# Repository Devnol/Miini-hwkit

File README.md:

# Miini hwkit
 Hardware schematics and PCB drawings for Nintendo Wii mini console add-ons.
 
### Project has moved permanently
 You can view the latest version [here](https://github.com/Wii-Mini-Hacking/miniRGBii)

 For more information visit [the Wii mini Hacking discord server](https://discord.gg/7jNHphfDQk)

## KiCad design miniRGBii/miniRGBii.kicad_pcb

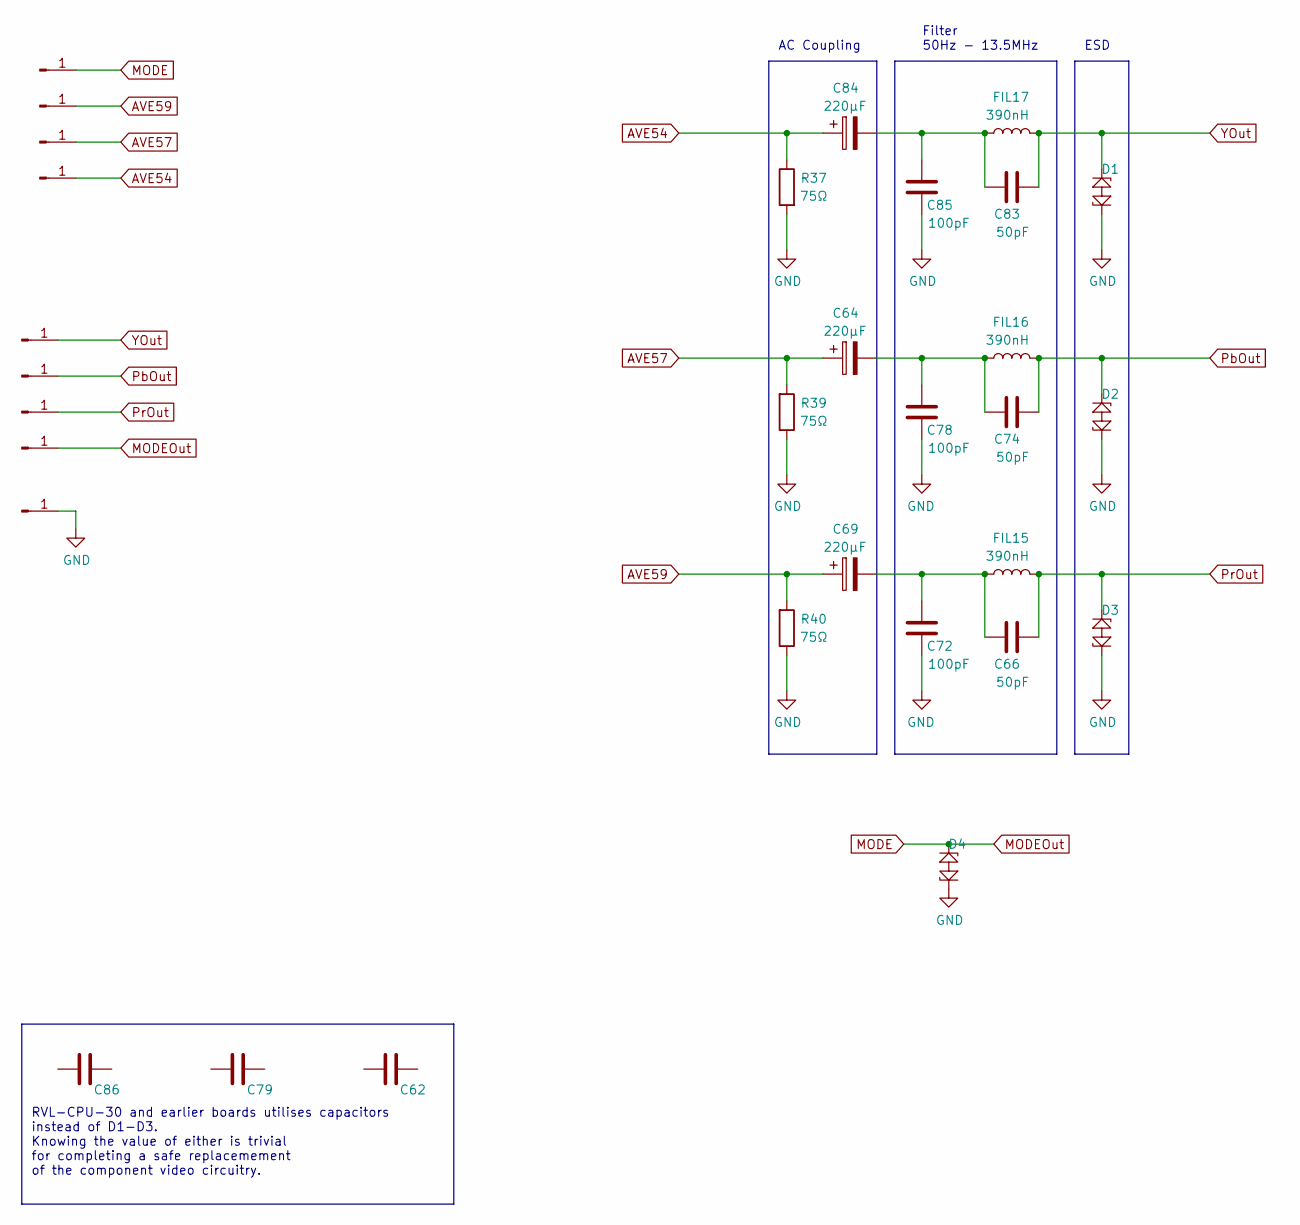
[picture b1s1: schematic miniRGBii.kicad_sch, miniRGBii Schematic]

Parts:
C62, C79, C86: 50pF
C64, C69, C84: 220μF; CP_EIA-7343-15_Kemet-W_Pad2.25x2.55mm_HandSolder
C66, C74, C83: 50pF; C_0603_1608Metric_Pad1.05x0.95mm_HandSolder
C72, C78, C85: 100pF; C_0603_1608Metric_Pad1.05x0.95mm_HandSolder
D1, D2, D3, D4: PESD5V0U1BA; D_SOD-323_HandSoldering
FIL15, FIL16, FIL17: 390nH; L_0603_1608Metric_Pad1.05x0.95mm_HandSolder
J1, J2, J3, J4, J5, J6, J7, J8, J9: Conn_01x01_Male; pad
R37, R39, R40: 75Ω; R_0603_1608Metric_Pad0.98x0.95mm_HandSolder

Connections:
AVE54: C84.1, J8.1, R37.1
AVE57: C64.1, J7.1, R39.2
AVE59: C69.1, J6.1, R40.2
GND: C72.1, C78.1, C85.1, D1.2, D2.2, D3.2, D4.2, J9.1, R37.2, R39.1, R40.1
MODE: D4.1, J4.1, J5.1
unnamed: C64.2, C74.1, C78.2, FIL16.2
unnamed: C66.1, C69.2, C72.2, FIL15.2
unnamed: C83.1, C84.2, C85.2, FIL17.2
PbOut: C74.2, D2.1, FIL16.1, J2.1
PrOut: C66.2, D3.1, FIL15.1, J3.1
YOut: C83.2, D1.1, FIL17.1, J1.1

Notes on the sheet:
RVL-CPU-30 and earlier boards utilises capacitors instead of D1-D3. Knowing the value of either is trivial for completing a safe replacemement of the component video circuitry.
Filter 50Hz - 13.5MHz
ESD
AC Coupling

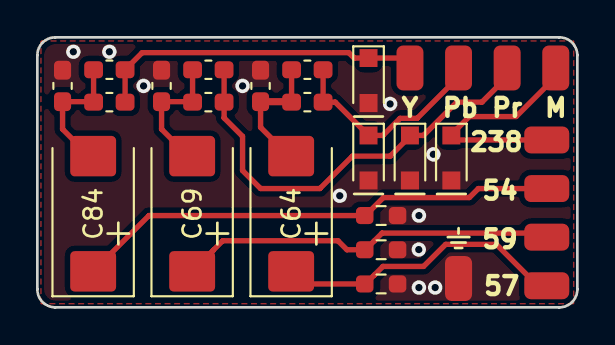
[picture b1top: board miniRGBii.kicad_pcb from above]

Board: 2 copper layers, 30.0 x 15.0 mm, 28 parts (0 on the bottom side), 11 nets.

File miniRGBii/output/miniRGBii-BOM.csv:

"Source:","/Users/User/Documents/CS_Projects/EDA/Miini-hwkit/miniRGBii/miniRGBii.kicad_sch"
"Date:","2022 February 26, Saturday 19:09:56"
"Tool:","Eeschema (6.0.0-0)"
"Generator:","/Applications/KiCad/KiCad.app/Contents/SharedSupport/plugins/bom_csv_grouped_by_value_with_fp.py"
"Component Count:","31"
"Ref","Qnty","Value","Cmp name","Footprint","Description","Vendor"
"C62, C79, C86, ","3","50pF","C","","Unpolarized capacitor",""
"C64, C69, C84, ","3","220μF","C_Polarized","Capacitor_Tantalum_SMD:CP_EIA-7343-15_Kemet-W_Pad2.25x2.55mm_HandSolder","Polarized capacitor",""
"C66, C74, C83, ","3","50pF","C","Capacitor_SMD:C_0603_1608Metric_Pad1.05x0.95mm_HandSolder","Unpolarized capacitor",""
"C72, C78, C85, ","3","100pF","C","Capacitor_SMD:C_0603_1608Metric_Pad1.05x0.95mm_HandSolder","Unpolarized capacitor",""
"D1, D2, D3, D4, ","4","PESD5V0U1BA","PESD5V0U1BA","Diode_SMD:D_SOD-323_HandSoldering","",""
"FIL15, FIL16, FIL17, ","3","390nH","L","Inductor_SMD:L_0603_1608Metric_Pad1.05x0.95mm_HandSolder","Inductor",""
"J1, J2, J3, J4, J5, J6, J7, J8, J9, ","9","Conn_01x01_Male","Conn_01x01_Male","Pad:pad","Generic connector, single row, 01x01, script generated (kicad-library-utils/schlib/autogen/connector/)",""
"R37, R39, R40, ","3","75Ω","R","Resistor_SMD:R_0603_1608Metric_Pad0.98x0.95mm_HandSolder","Resistor",""

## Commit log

2020-05-26 Added HDTVii, an add-on board for Component video (Incomplete, untested)
2020-05-26 Updated SVG and PDF files
2020-06-04 forgotten to commit this idk
2020-06-30 Changed some stuff around I guess
2020-06-30 Added footprints
2020-07-06 Added correct (hopefully) inductor values. Credit to Job Feikens for the values
2020-07-09 Created PCB design and added footprint refs to parts.
    Also changed stuff in the Schematic
2020-07-09 Renamed project, trimmed pcb design
2020-07-23 Changed many things
2020-07-23 Added PDF and SVG for easy viewing
2020-07-28 Changed schematic to look less tangled
2020-07-28 At least there's the net on pcbnew to remind me how big of a moron I am.
    I had mixed up some parts while shifting the schematic around/
2020-07-28 Changed the board to utilise lower profile capacitors
2020-08-28 Removed everything from the master branch
2020-08-28 Copied Job's design to the master branch and changed the naming of the designs
2020-08-29 removed old rear solder mask gerbers
2020-08-29 Added 20-pack stencil for large production.
    Also moved a GND via that was too close to a data line
2020-08-30 renamed to panel cuz I'm dumb
2020-08-30 added images folder for people without KiCAD and made curved edges
2020-08-30 Changed url to lowercase, moved vias around
2020-08-30 finalised (hopefully) the panel version
2020-08-30 made a new output.zip
2020-12-07 added gitignore
2020-12-07 edited gitignore
2020-12-09 mentioned wiiniidsdii
2020-12-09 Added files
2020-12-14 Rename WiiNiidSDii/.gitkeep to WiiniSDii
2020-12-14 Create ,gitkeep
2021-01-07 change discord username
2021-02-11 Rename ReadMii.md to README.md
2022-02-26 Add Bill Of Materials for miniRGBii
2022-02-26 migrate miniRGBii to KiCAD 6
2022-02-26 That shouldn't have been removed
2022-02-26 remove miniRGBii_panel, may be added back after update has finished
2022-02-26 Fix 3d model directories for KiCAD 6
2022-02-26 export to pdf, svg, gerber and more
2022-03-01 move project to Wii mini Hacking org
